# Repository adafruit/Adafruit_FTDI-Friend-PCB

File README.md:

# Adafruit FTDI Friend

<a href="http://www.adafruit.com/products/284"><br/>Click here to purchase one from the Adafruit shop</a>

Long gone are the days of parallel ports and serial ports. Now the USB port reigns supreme! But USB is hard, and you just want to transfer your every-day serial data from a microcontroller to computer. What now? Enter the FTDI Friend!

The FTDI Friend is a tweaked out FTDI FT232RL chip adapter. Sure, like the well-known FTDI cable, it can provide power to your project and there are 4 signal lines for sending data back and forth. But the Friend can do much more! For example, you can change the signal and power lines to be either 3.3V or 5V. Arduino-derivatives and XBees use the RTS line for programming but what if you need that DTR line? It's there for you.
By default, we've set it up so that it matches our FTDI cables. The 6th pin is RTS (as of Arduino IDE v18 this will work perfectly for uploading to 'inos), the power wire is +5V and the signal levels are 3.3V (they are 5V compliant, and should work in the vast majority of 3.3V and 5V signal systems).

And of course, we include __a little extra__ - in this case its the extra-long headers that you can use to plug it into a breadboard. There are also blinkies, 2 red & green LEDs __already on the board__ that pulse when serial is sent or received.

Revision History:

* As of December 5, 2023 - We've updated this board with a micro USB-B connector as well as used Adafruit Pinguin to make a lovely silkscreen.

### License

Adafruit invests time and resources providing this open source design, please support Adafruit and open-source hardware by purchasing products from [Adafruit](https://www.adafruit.com)!

Designed by Limor Fried/Ladyada for Adafruit Industries.

Creative Commons Attribution/Share-Alike, all text above must be included in any redistribution. See license.txt for additional details.

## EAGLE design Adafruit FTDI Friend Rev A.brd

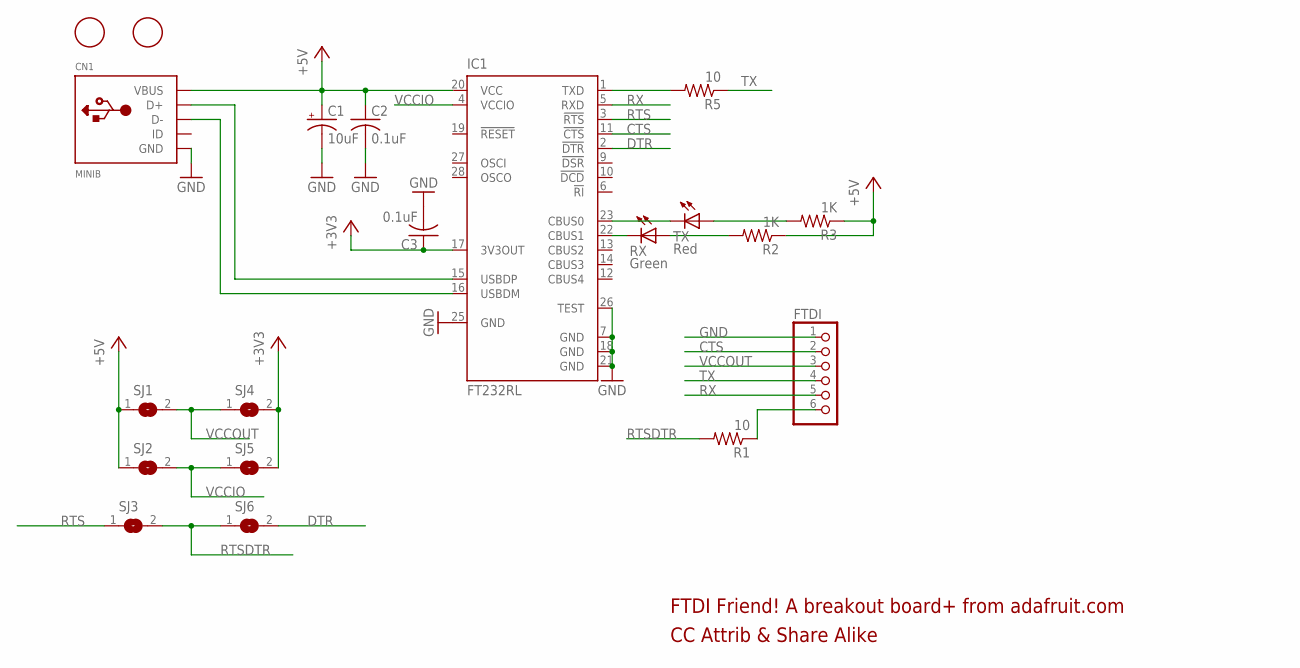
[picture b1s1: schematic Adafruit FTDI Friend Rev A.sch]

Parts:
C1: 10uF; A/3216-18R
C2, C3: 0.1uF; C0805K
CN1: MINIB; USB-MINIB
FTDI: PINHD-1X6CB; 1X06-CLEANBIG
IC1: FT232RL; SSOP28
R1, R5: 10; R0805
R2, R3: 1K; R0805
RX: Green; CHIP-LED0805
SJ1, SJ2, SJ3, SJ4, SJ5, SJ6: SJ
TX: Red; CHIP-LED0805
U$1, U$2: FIDUCIAL; FIDUCIAL_1MM

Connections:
+3V3: C3.1, IC1.17 (3V3OUT), SJ4.2, SJ5.2
+5V: C1.+, C2.1, CN1.VBUS, IC1.20 (VCC), R2.1, R3.1, SJ1.1, SJ2.1
CTS: FTDI.2, IC1.11 (!CTS)
DTR: IC1.2 (!DTR), SJ6.2
GND: C1.-, C2.2, C3.2, CN1.GND, FTDI.1, IC1.7 (GND), IC1.18 (GND), IC1.21 (GND), IC1.25 (GND), IC1.26 (TEST)
unnamed: FTDI.6, R1.1
unnamed: CN1.D+, IC1.15 (USBDP)
unnamed: CN1.D-, IC1.16 (USBDM)
unnamed: IC1.1 (TXD), R5.2
unnamed: IC1.23 (CBUS0), TX.C
unnamed: IC1.22 (CBUS1), RX.C
unnamed: R2.2, RX.A
unnamed: R3.2, TX.A
RTS: IC1.3 (!RTS), SJ3.1
RTSDTR: R1.2, SJ3.2, SJ6.1
RX: FTDI.5, IC1.5 (RXD)
TX: FTDI.4, R5.1
VCCIO: IC1.4 (VCCIO), SJ2.2, SJ5.1
VCCOUT: FTDI.3, SJ1.2, SJ4.1

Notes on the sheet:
CC Attrib & Share Alike
FTDI Friend! A breakout board+ from adafruit.com

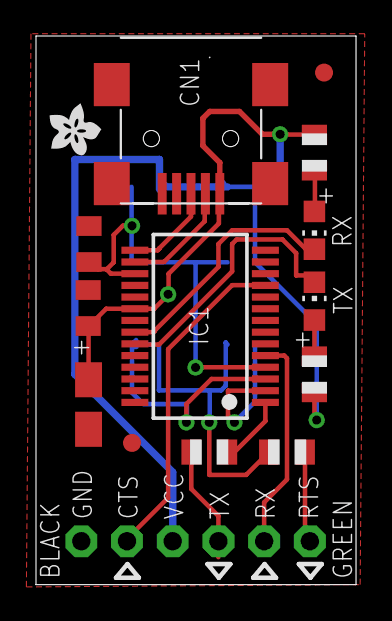
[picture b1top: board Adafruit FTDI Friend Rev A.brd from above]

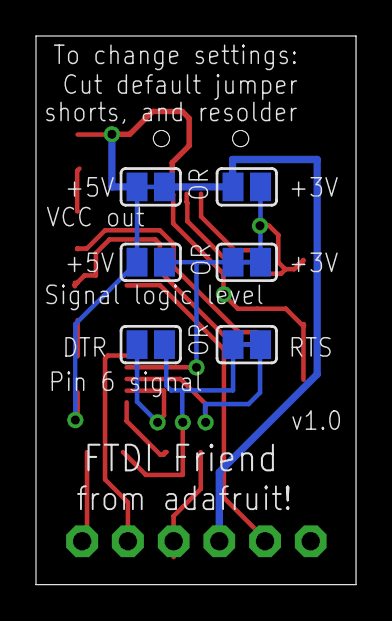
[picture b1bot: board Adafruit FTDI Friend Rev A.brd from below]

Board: 2 copper layers, 17.8 x 30.5 mm, 21 parts (6 on the bottom side), 19 nets.

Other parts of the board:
U$3: ADAFRUIT200MIL

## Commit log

2010-09-13 v1.0 for release!
2010-09-13 Schematic image
2019-03-15 image & new readme
2023-12-08 adding rev B files
2026-06-03 update file format to XML
